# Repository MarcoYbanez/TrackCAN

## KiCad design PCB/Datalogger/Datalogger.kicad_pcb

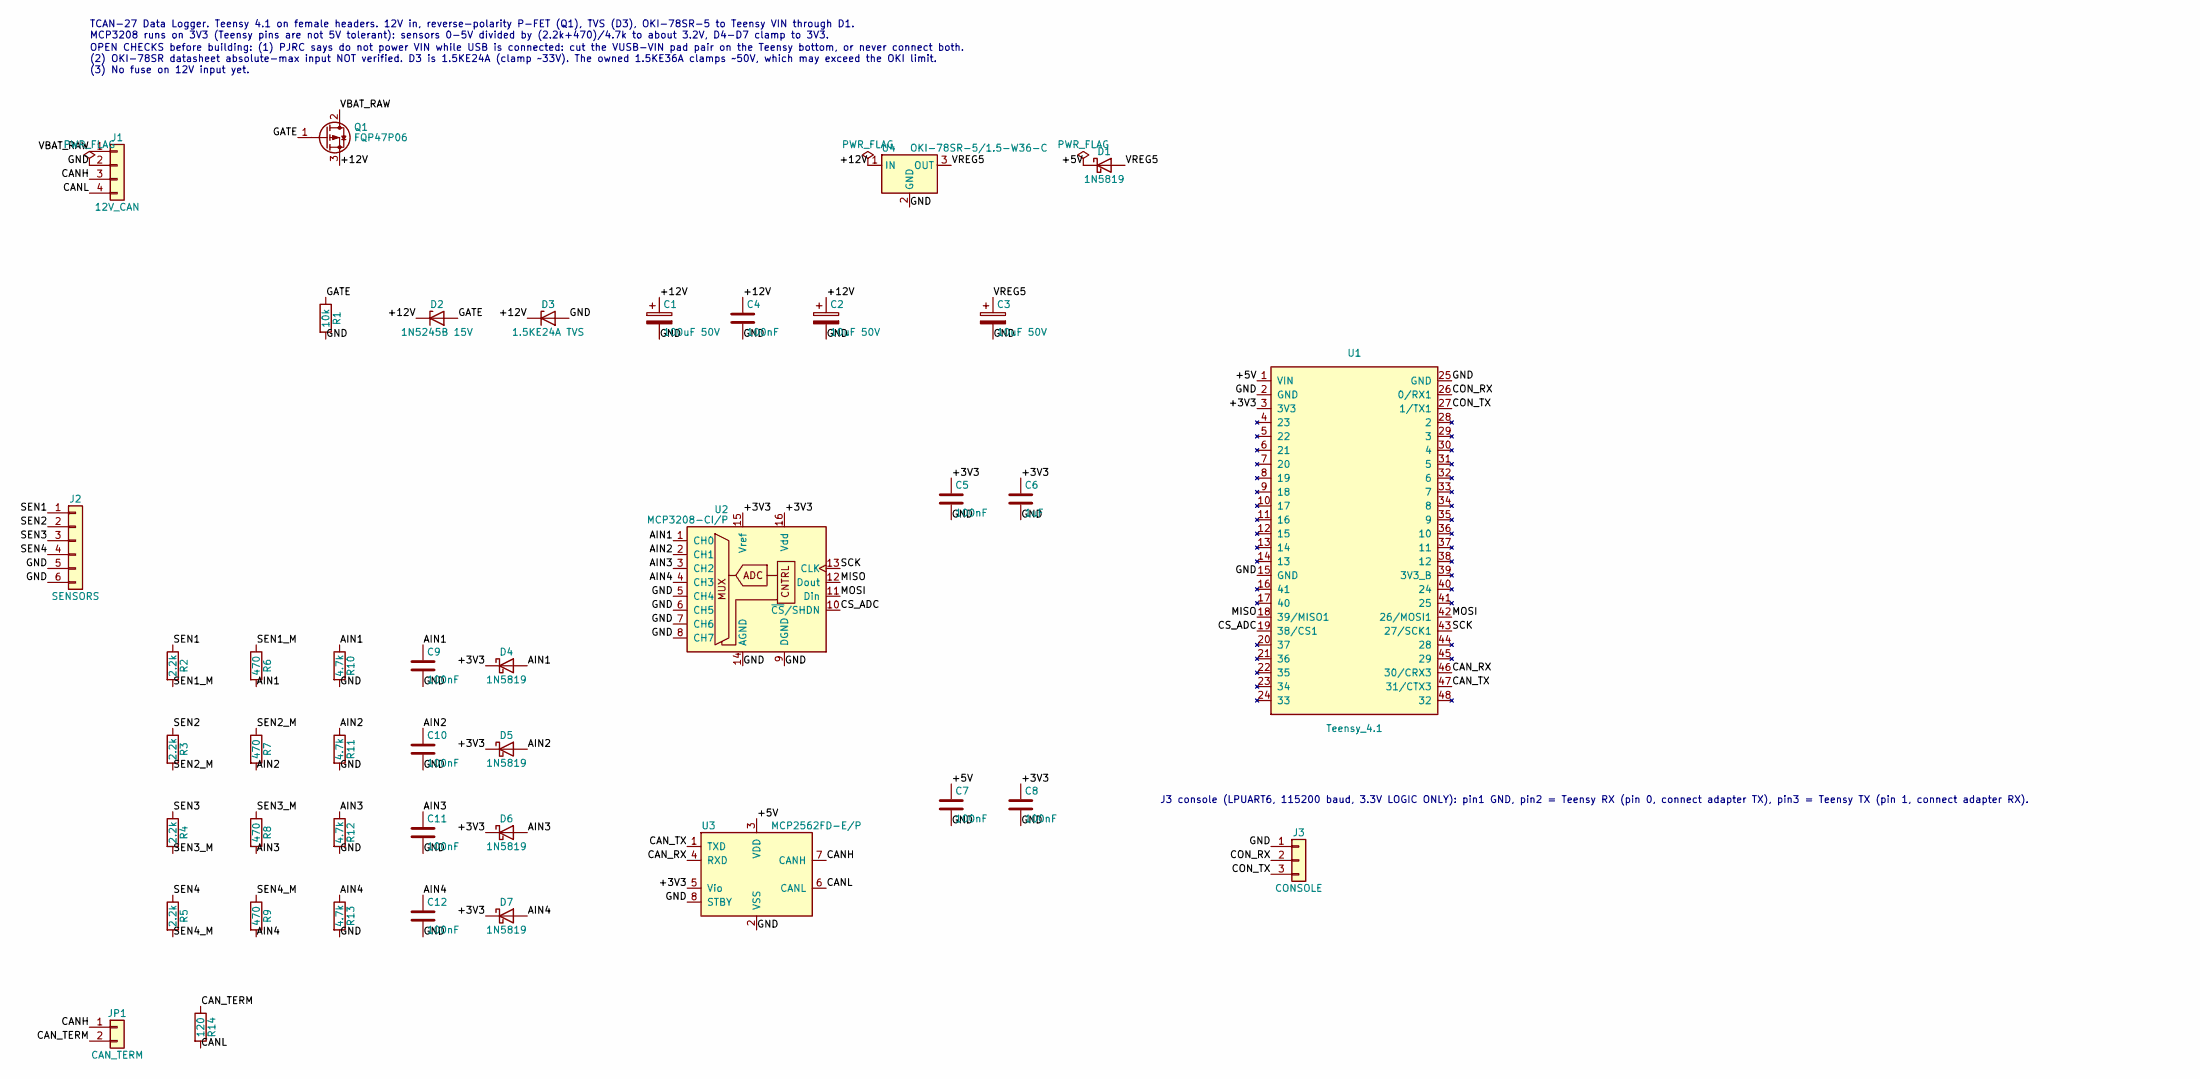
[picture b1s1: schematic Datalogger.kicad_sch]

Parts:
C1: 100uF 50V; CP_Radial_D8.0mm_P3.50mm
C2, C3: 10uF 50V; CP_Radial_D5.0mm_P2.00mm
C4, C5, C7, C8, C9, C10, C11, C12: 100nF; C_Disc_D5.0mm_W2.5mm_P5.00mm
C6: 1uF; C_Disc_D5.0mm_W2.5mm_P5.00mm
D1, D4, D5, D6, D7: 1N5819; D_DO-41_SOD81_P10.16mm_Horizontal
D2: 1N5245B 15V; D_DO-35_SOD27_P7.62mm_Horizontal
D3: 1.5KE24A TVS; D_DO-201AD_P15.24mm_Horizontal
J1: 12V_CAN; Molex_KK-254_AE-6410-04A_1x04_P2.54mm_Vertical
J2: SENSORS; Molex_KK-254_AE-6410-06A_1x06_P2.54mm_Vertical
J3: CONSOLE; PinHeader_1x03_P2.54mm_Vertical
JP1: CAN_TERM; PinHeader_1x02_P2.54mm_Vertical
Q1: FQP47P06; TO-220-3_Vertical
R1: 10k; R_Axial_DIN0207_L6.3mm_D2.5mm_P7.62mm_Horizontal
R2, R3, R4, R5: 2.2k; R_Axial_DIN0207_L6.3mm_D2.5mm_P7.62mm_Horizontal
R6, R7, R8, R9: 470; R_Axial_DIN0207_L6.3mm_D2.5mm_P7.62mm_Horizontal
R10, R11, R12, R13: 4.7k; R_Axial_DIN0207_L6.3mm_D2.5mm_P7.62mm_Horizontal
R14: 120; R_Axial_DIN0207_L6.3mm_D2.5mm_P7.62mm_Horizontal
U1: Teensy_4.1; Teensy_4.1_Sockets_2x24_P2.54mm_W15.24mm
U2: MCP3208-CI/P; DIP-16_W7.62mm
U3: MCP2562FD-E/P; DIP-8_W7.62mm
U4: OKI-78SR-5/1.5-W36-C; Converter_DCDC_Murata_OKI-78SR_Vertical

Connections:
/+3V3: C5.1, C6.1, C8.1, D4.1 (K), D5.1 (K), D6.1 (K), D7.1 (K), U1.3 (3V3), U2.15 (Vref), U2.16 (Vdd), U3.5 (Vio)
/AIN1: C9.1, D4.2 (A), R6.2, R10.1, U2.1 (CH0)
/AIN2: C10.1, D5.2 (A), R7.2, R11.1, U2.2 (CH1)
/AIN3: C11.1, D6.2 (A), R8.2, R12.1, U2.3 (CH2)
/AIN4: C12.1, D7.2 (A), R9.2, R13.1, U2.4 (CH3)
/CANH: J1.3, JP1.1, U3.7 (CANH)
/CANL: J1.4, R14.2, U3.6 (CANL)
/CAN_RX: U1.46 (30/CRX3), U3.4 (RXD)
/CAN_TERM: JP1.2, R14.1
/CAN_TX: U1.47 (31/CTX3), U3.1 (TXD)
/CON_RX: J3.2, U1.26 (0/RX1)
/CON_TX: J3.3, U1.27 (1/TX1)
/CS_ADC: U1.19 (38/CS1), U2.10 (~CS/SHDN)
/GATE: D2.2 (A), Q1.1 (G), R1.1
/MISO: U1.18 (39/MISO1), U2.12 (Dout)
/MOSI: U1.42 (26/MOSI1), U2.11 (Din)
/SCK: U1.43 (27/SCK1), U2.13 (CLK)
/SEN1: J2.1, R2.1
/SEN1_M: R2.2, R6.1
/SEN2: J2.2, R3.1
/SEN2_M: R3.2, R7.1
/SEN3: J2.3, R4.1
/SEN3_M: R4.2, R8.1
/SEN4: J2.4, R5.1
/SEN4_M: R5.2, R9.1
/VBAT_RAW: J1.1, Q1.2 (D)
/VREG5: C3.1, D1.2 (A), U4.3 (OUT)

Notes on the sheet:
TCAN-27 Data Logger. Teensy 4.1 on female headers. 12V in, reverse-polarity P-FET (Q1), TVS (D3), OKI-78SR-5 to Teensy VIN through D1. MCP3208 runs on 3V3 (Teensy pins are not 5V tolerant): sensors 0-5V divided by (2.2k+470)/4.7k to about 3.2V, D4-D7 clamp to 3V3.
OPEN CHECKS before building: (1) PJRC says do not power VIN while USB is connected: cut the VUSB-VIN pad pair on the Teensy bottom, or never connect both. (2) OKI-78SR datasheet absolute-max input NOT verified. D3 is 1.5KE24A (clamp ~33V). The owned 1.5KE36A clamps ~50V, which may exceed the OKI li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
J3 console (LPUART6, 115200 baud, 3.3V LOGIC ONLY): pin1 GND, pin2 = Teensy RX (pin 0, connect adapter TX), pin3 = Teensy TX (pin 1, connect adapter RX).

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
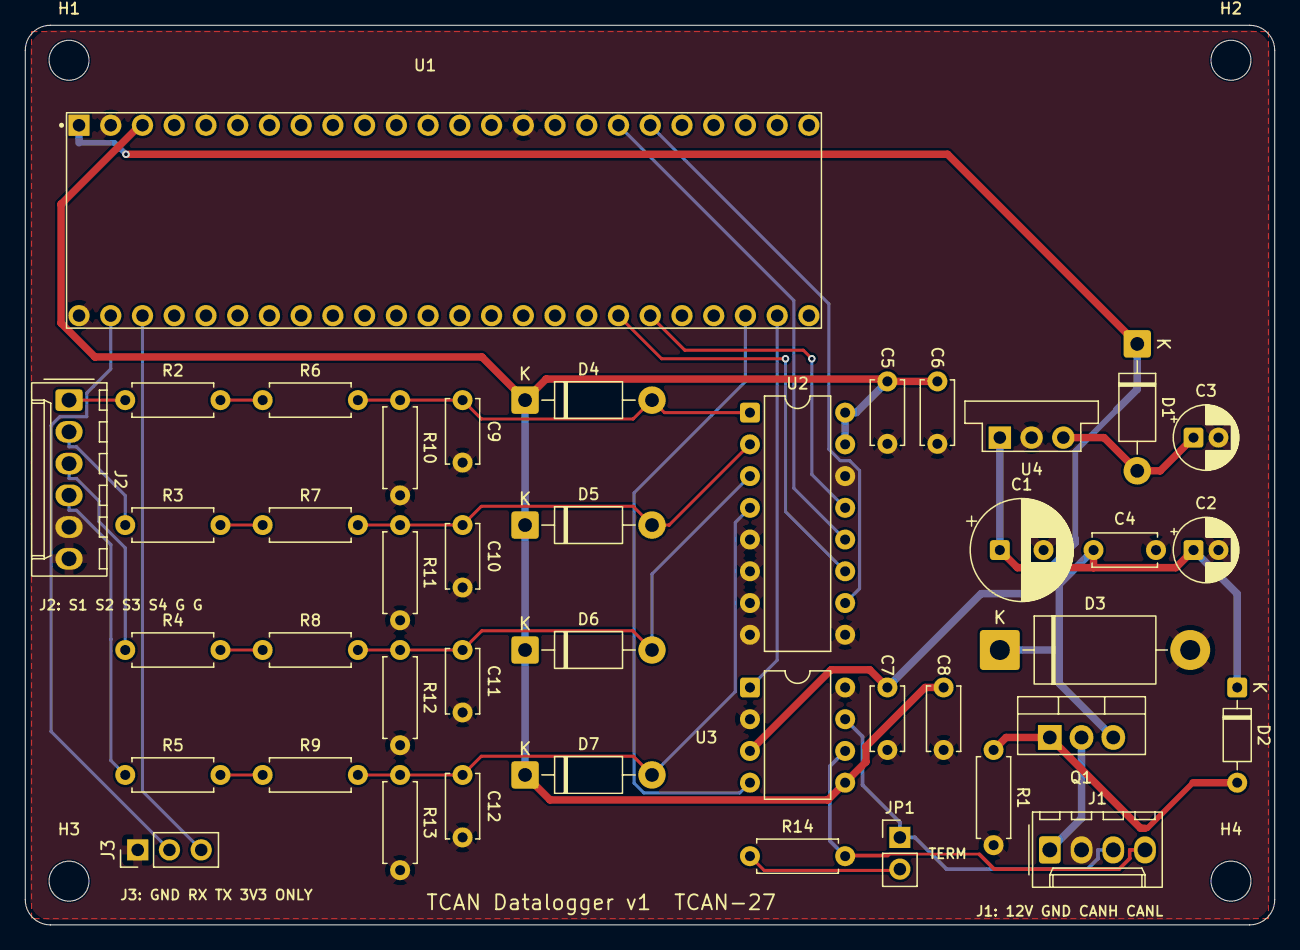
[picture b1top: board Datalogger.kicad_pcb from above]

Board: 2 copper layers, 100.0 x 72.0 mm, 46 parts (0 on the bottom side), 30 nets.

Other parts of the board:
H1, H2, H3, H4: MountingHole_3.2mm_M3
